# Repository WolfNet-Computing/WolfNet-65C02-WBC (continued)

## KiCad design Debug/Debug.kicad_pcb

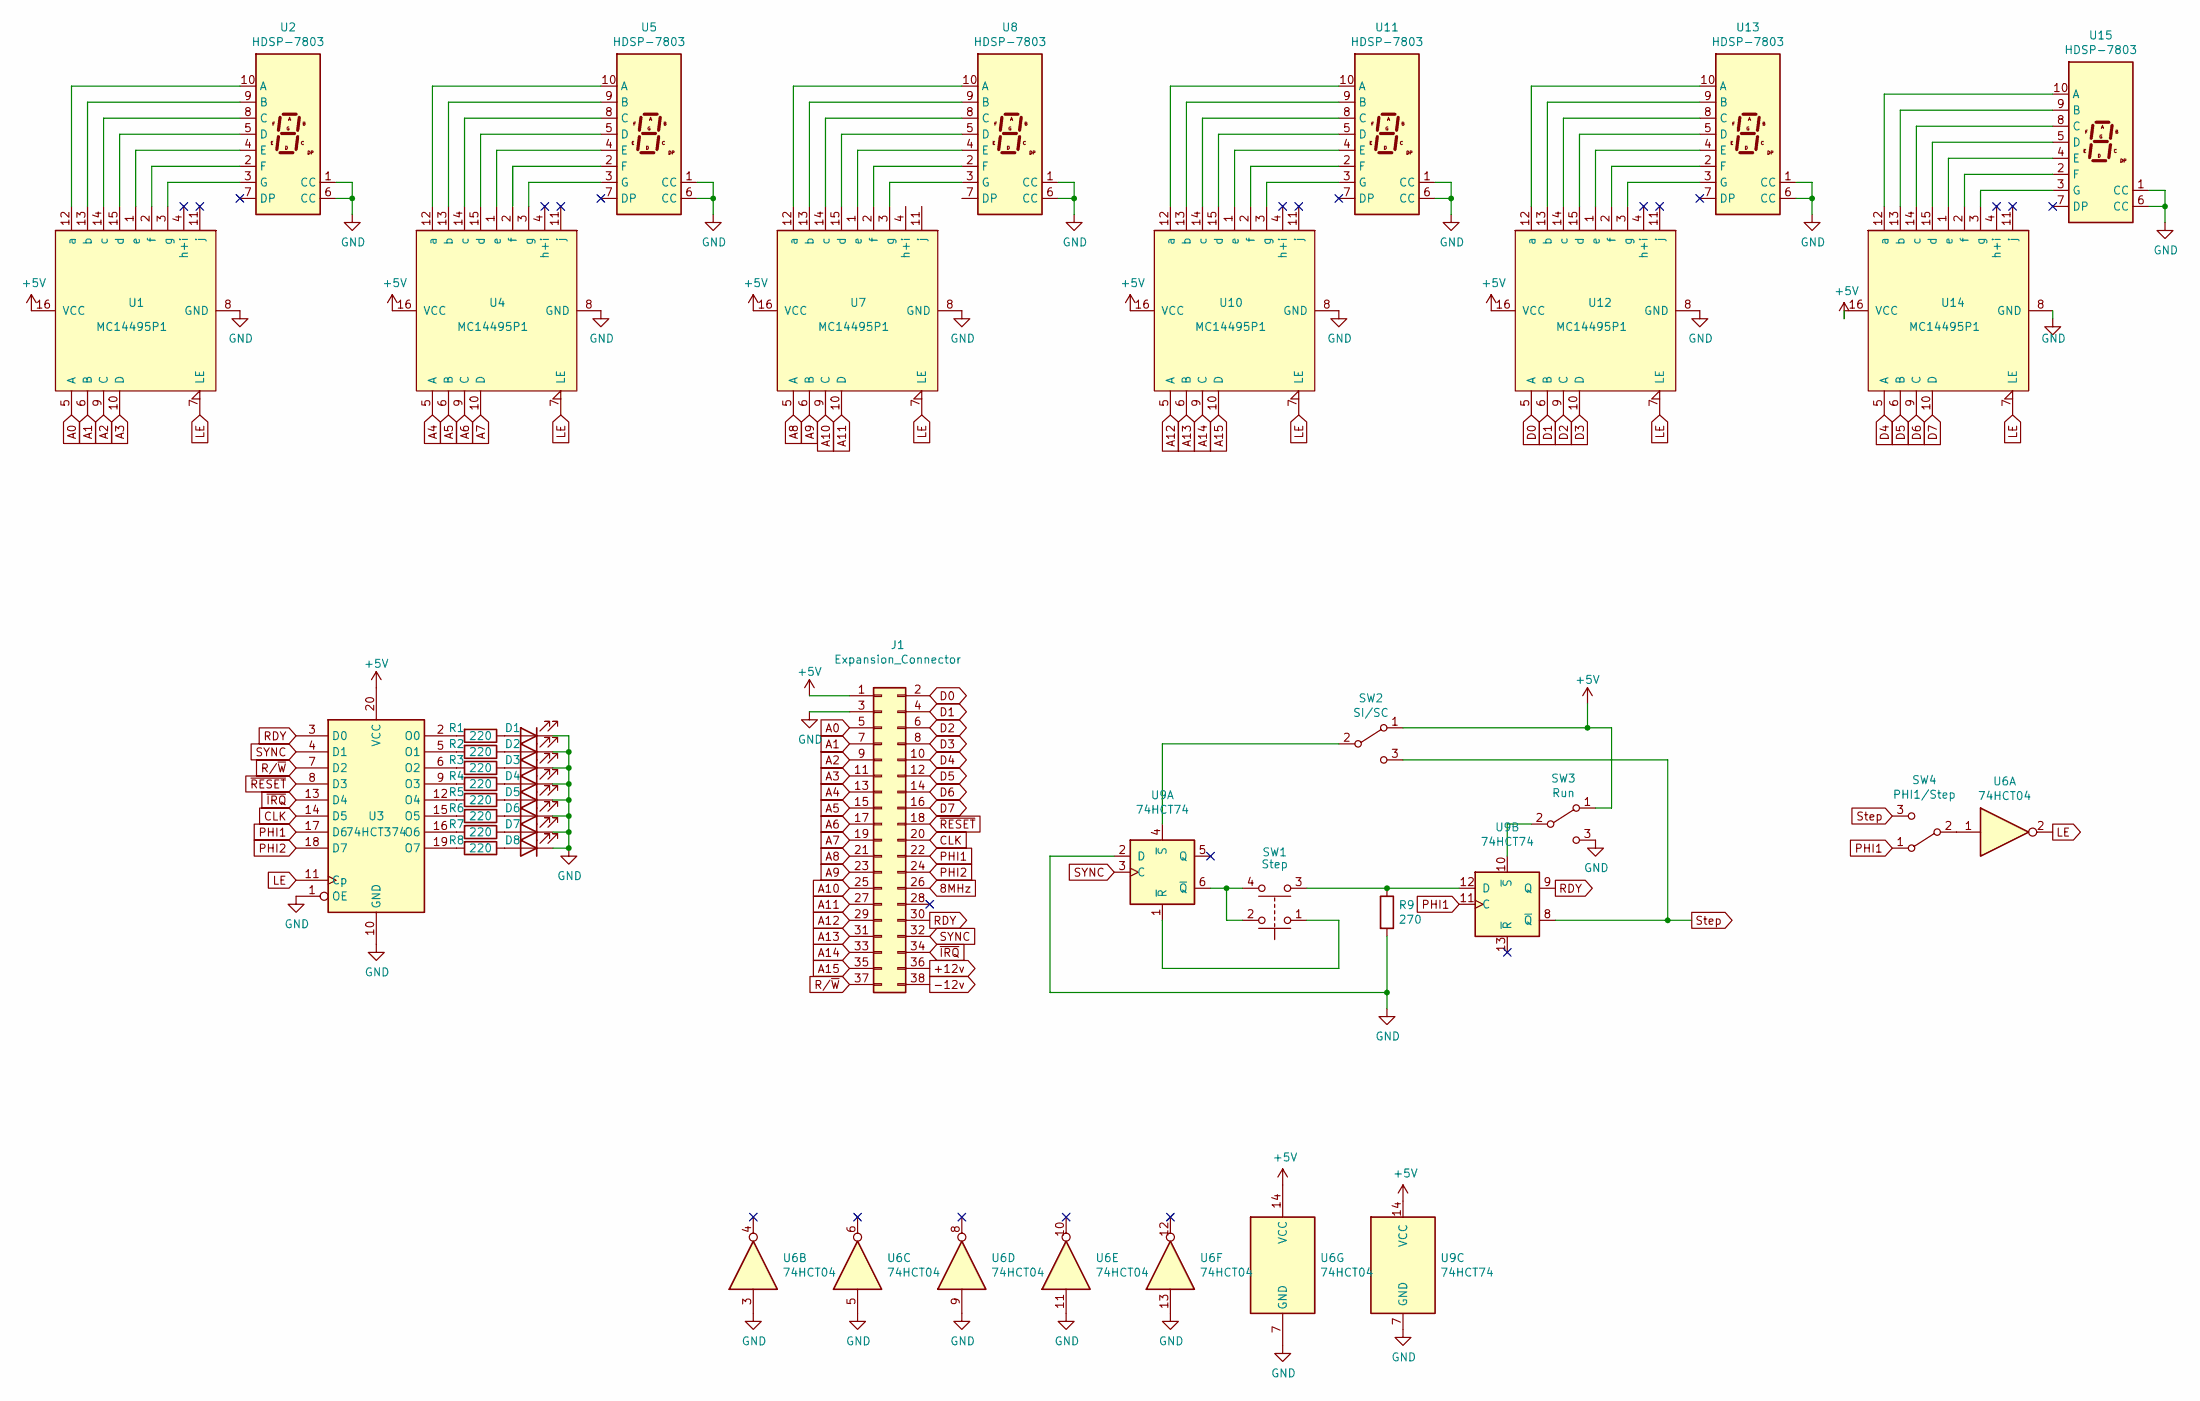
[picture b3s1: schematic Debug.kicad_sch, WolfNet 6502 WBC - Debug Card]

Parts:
D1: RDY; LED_D5.0mm
D2: Sync; LED_D5.0mm
D3: RW; LED_D5.0mm
D4: Reset; LED_D5.0mm
D5: IRQ; LED_D5.0mm
D6: NMI; LED_D5.0mm
D7: PHI1; LED_D5.0mm
D8: PHI2; LED_D5.0mm
J1: Expansion_Connector; PinHeader_2x19_P2.54mm_Horizontal
R1, R2, R3, R4, R5, R6, R7, R8: 220; R_Axial_DIN0207_L6.3mm_D2.5mm_P7.62mm_Horizontal
R9: 270; R_Axial_DIN0207_L6.3mm_D2.5mm_P7.62mm_Horizontal
SW1: Step; SW_Push_2P1T_Toggle_CK_PVA1xxH1xxxxxxV2
SW2: SI/SC; SW_Slide_1P2T_CK_OS102011MS2Q
SW3: Run; SW_Slide_1P2T_CK_OS102011MS2Q
SW4: PHI1/Step; SW_Slide_1P2T_CK_OS102011MS2Q
U1, U4, U7, U10, U12, U14: MC14495P1; DIP-16_W7.62mm_Socket_LongPads
U2, U5, U8, U11, U13, U15: HDSP-7803; HDSP-7801
U3: 74HCT374; DIP-20_W7.62mm_Socket_LongPads
U6: 74HCT04; DIP-14_W7.62mm_Socket_LongPads
U9: 74HCT74; DIP-14_W7.62mm_Socket_LongPads

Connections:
8MHz: J1.26
+5V: J1.1, SW2.1 (A), SW3.1 (A), U1.16 (VCC), U3.20 (VCC), U4.16 (VCC), U6.14 (VCC), U7.16 (VCC), U9.14 (VCC), U10.16 (VCC), U12.16 (VCC), U14.16 (VCC)
+12v: J1.36
-12v: J1.38
A0: J1.5, U1.5 (A)
A1: J1.7, U1.6 (B)
A2: J1.9, U1.9 (C)
A3: J1.11, U1.10 (D)
A4: J1.13, U4.5 (A)
A5: J1.15, U4.6 (B)
A6: J1.17, U4.9 (C)
A7: J1.19, U4.10 (D)
A8: J1.21, U7.5 (A)
A9: J1.23, U7.6 (B)
A10: J1.25, U7.9 (C)
A11: J1.27, U7.10 (D)
A12: J1.29, U10.5 (A)
A13: J1.31, U10.6 (B)
A14: J1.33, U10.9 (C)
A15: J1.35, U10.10 (D)
CLK: J1.20, U3.14 (D5)
D0: J1.2, U12.5 (A)
D1: J1.4, U12.6 (B)
D2: J1.6, U12.9 (C)
D3: J1.8, U12.10 (D)
D4: J1.10, U14.5 (A)
D5: J1.12, U14.6 (B)
D6: J1.14, U14.9 (C)
D7: J1.16, U14.10 (D)
GND: D1.1 (K), D2.1 (K), D3.1 (K), D4.1 (K), D5.1 (K), D6.1 (K), D7.1 (K), D8.1 (K), J1.3, R9.2, SW3.3 (C), U1.8 (GND), U2.1 (CC), U2.6 (CC), U3.1 (OE), U3.10 (GND), U4.8 (GND), U5.1 (CC), U5.6 (CC), U6.3, U6.5, U6.7 (GND), U6.9, U6.11, U6.13, U7.8 (GND), U8.1 (CC), U8.6 (CC), U9.2 (D), U9.7 (GND), U10.8 (GND), U11.1 (CC), U11.6 (CC), U12.8 (GND), U13.1 (CC), U13.6 (CC), U14.8 (GND), U15.1 (CC), U15.6 (CC)
LE: U1.7 (LE), U3.11 (Cp), U4.7 (LE), U6.2, U7.7 (LE), U10.7 (LE), U12.7 (LE), U14.7 (LE)
unnamed: D1.2 (A), R1.1
unnamed: D2.2 (A), R2.1
unnamed: D3.2 (A), R3.1
unnamed: D4.2 (A), R4.1
unnamed: D5.2 (A), R5.1
unnamed: D6.2 (A), R6.1
unnamed: D7.2 (A), R7.1
unnamed: D8.2 (A), R8.1
unnamed: SW2.2 (B), U9.4 (~S)
unnamed: SW3.2 (B), U9.10 (~S)
unnamed: SW4.2 (B), U6.1
unnamed: U1.12 (a), U2.10 (A)
unnamed: U1.13 (b), U2.9 (B)
unnamed: U1.14 (c), U2.8 (C)
unnamed: U1.15 (d), U2.5 (D)
unnamed: U1.1 (e), U2.4 (E)
unnamed: U1.2 (f), U2.2 (F)
unnamed: U1.3 (g), U2.3 (G)
unnamed: R1.2, U3.2 (O0)
unnamed: R2.2, U3.5 (O1)
unnamed: R3.2, U3.6 (O2)
unnamed: R4.2, U3.9 (O3)
unnamed: R5.2, U3.12 (O4)
unnamed: R6.2, U3.15 (O5)
unnamed: R7.2, U3.16 (O6)
unnamed: R8.2, U3.19 (O7)
unnamed: U4.12 (a), U5.10 (A)
unnamed: U4.13 (b), U5.9 (B)
unnamed: U4.14 (c), U5.8 (C)
unnamed: U4.15 (d), U5.5 (D)
unnamed: U4.1 (e), U5.4 (E)
unnamed: U4.2 (f), U5.2 (F)
unnamed: U4.3 (g), U5.3 (G)
unnamed: U7.12 (a), U8.10 (A)
unnamed: U7.13 (b), U8.9 (B)
unnamed: U7.14 (c), U8.8 (C)
unnamed: U7.15 (d), U8.5 (D)
unnamed: U7.1 (e), U8.4 (E)
unnamed: U7.2 (f), U8.2 (F)
unnamed: U7.3 (g), U8.3 (G)
unnamed: SW1.2, SW1.4, U9.6 (~Q)
unnamed: SW1.1, U9.1 (~R)
unnamed: R9.1, SW1.3, U9.12 (D)
unnamed: U10.12 (a), U11.10 (A)
unnamed: U10.13 (b), U11.9 (B)
unnamed: U10.14 (c), U11.8 (C)
unnamed: U10.15 (d), U11.5 (D)
unnamed: U10.1 (e), U11.4 (E)
unnamed: U10.2 (f), U11.2 (F)
unnamed: U10.3 (g), U11.3 (G)
unnamed: U12.12 (a), U13.10 (A)
unnamed: U12.13 (b), U13.9 (B)
unnamed: U12.14 (c), U13.8 (C)
unnamed: U12.15 (d), U13.5 (D)
unnamed: U12.1 (e), U13.4 (E)
unnamed: U12.2 (f), U13.2 (F)
unnamed: U12.3 (g), U13.3 (G)
unnamed: U14.12 (a), U15.10 (A)
unnamed: U14.13 (b), U15.9 (B)
unnamed: U14.14 (c), U15.8 (C)
unnamed: U14.15 (d), U15.5 (D)
unnamed: U14.1 (e), U15.4 (E)
unnamed: U14.2 (f), U15.2 (F)
unnamed: U14.3 (g), U15.3 (G)
PHI1: J1.22, SW4.1 (A), U3.17 (D6), U9.11 (C)
PHI2: J1.24, U3.18 (D7)
RDY: J1.30, U3.3 (D0), U9.9 (Q)
R/~W: J1.37, U3.7 (D2)
SYNC: J1.32, U3.4 (D1), U9.3 (C)
Step: SW2.3 (C), SW4.3 (C), U9.8 (~Q)
~IRQ: J1.34, U3.13 (D4)
~RESET: J1.18, U3.8 (D3)

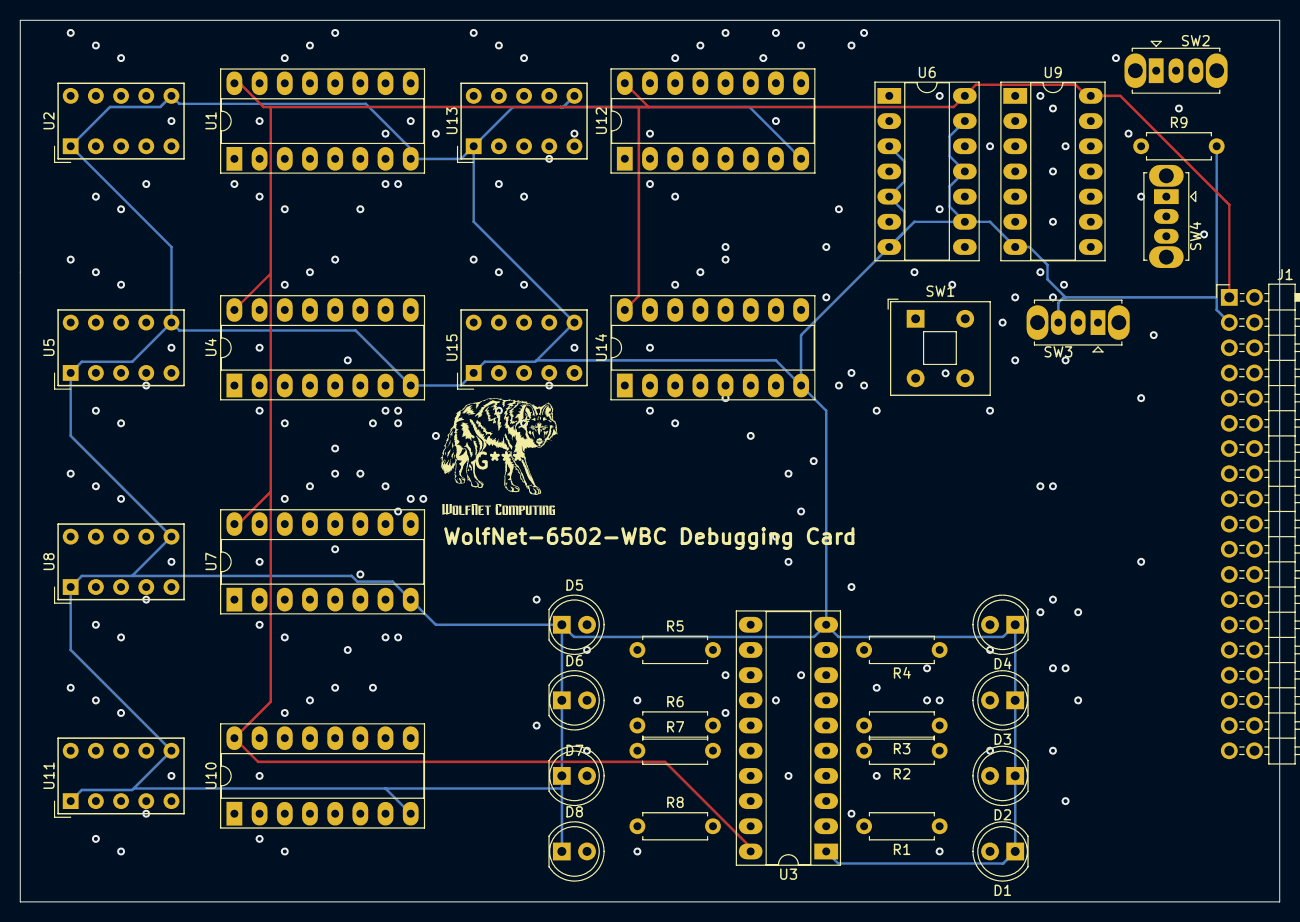
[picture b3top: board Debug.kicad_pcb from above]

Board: 4 copper layers, 127.0 x 88.9 mm, 37 parts (0 on the bottom side), 100 nets.

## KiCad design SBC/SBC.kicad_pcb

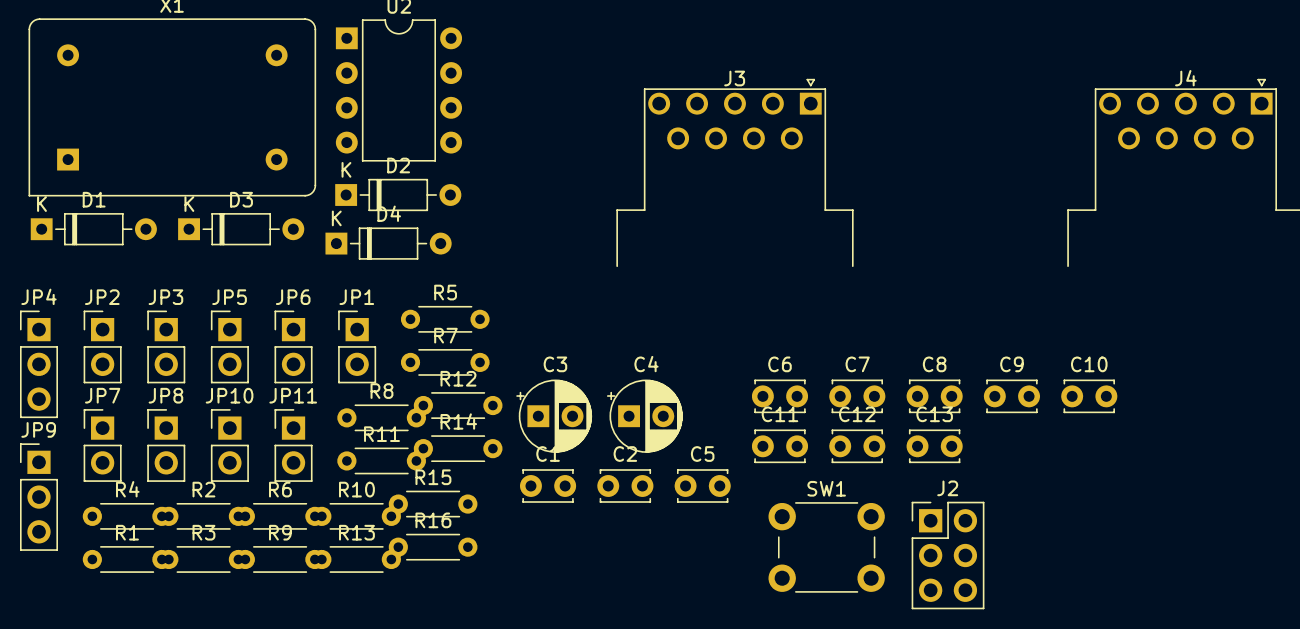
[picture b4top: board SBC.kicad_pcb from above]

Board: 2 copper layers, 50 parts (0 on the bottom side), 14 nets, no tracks yet.

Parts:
C1, C2, C5, C6, C7, C8, C9, C10, C11, C12, C13: C; C_Disc_D3.4mm_W2.1mm_P2.50mm
C3, C4: CP; CP_Radial_D5.0mm_P2.50mm
D1, D2, D3, D4: 1N4148; D_DO-35_SOD27_P7.62mm_Horizontal
J2: GPIO_Connector; PinHeader_2x03_P2.54mm_Vertical
J3, J4: DB9_Male; DSUB-9_Female_Horizontal_P2.77x2.54mm_EdgePinOffset9.40mm
JP1, JP2, JP3, JP6, JP7, JP8, JP10: Jumper_2_Bridged; PinHeader_1x02_P2.54mm_Vertical
JP4: Jumper_3_Open; PinHeader_1x03_P2.54mm_Vertical
JP5, JP11: Jumper_2_Open; PinHeader_1x02_P2.54mm_Vertical
JP9: Jumper_3_Bridged12; PinHeader_1x03_P2.54mm_Vertical
R1, R2, R3: 3.3k; R_Axial_DIN0204_L3.6mm_D1.6mm_P5.08mm_Horizontal
R4, R5, R6, R7, R8, R9, R10, R11, R12, R13, R14, R15, R16: R; R_Axial_DIN0204_L3.6mm_D1.6mm_P5.08mm_Horizontal
SW1: SW_Push; SW_PUSH_6mm
U2: NE555P; DIP-8_W7.62mm
X1: ACO-xxxMHz; Oscillator_DIP-14

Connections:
CLK: JP6.2, JP7.2, JP8.2
CLK1: JP6.1, X1.8
GND: C1.2, C2.2, C3.2, C4.2, C5.2, C6.2, C7.2, C8.2, C9.2, C10.1, C11.1, C12.1, C13.1, D1.2, D3.1, J3.5, J3.9, J4.5, J4.9, JP3.1, R16.1, SW1.2, U2.1, X1.7
unnamed: C1.1, SW1.1, U2.2
unnamed: C3.1, R4.2, U2.6, U2.7
unnamed: C4.1, D2.1, D4.2, JP4.3
unnamed: C7.1, JP4.2, JP5.1
unnamed: D1.1, D2.2
unnamed: D3.2, D4.1
unnamed: JP1.2, R3.1
unnamed: JP2.2, R2.1
unnamed: JP10.2, R16.2
PG: JP10.1, JP11.1
VCC: C2.1, C5.1, C6.1, C8.1, C9.1, C10.2, C11.2, C12.2, C13.2, JP5.2, R1.2, R2.2, R3.2, R4.1, R5.2, R6.1, R7.1, R8.1, R9.1, R10.1, R11.1, R12.1, R13.1, R14.1, R15.2, U2.4, U2.8, X1.14

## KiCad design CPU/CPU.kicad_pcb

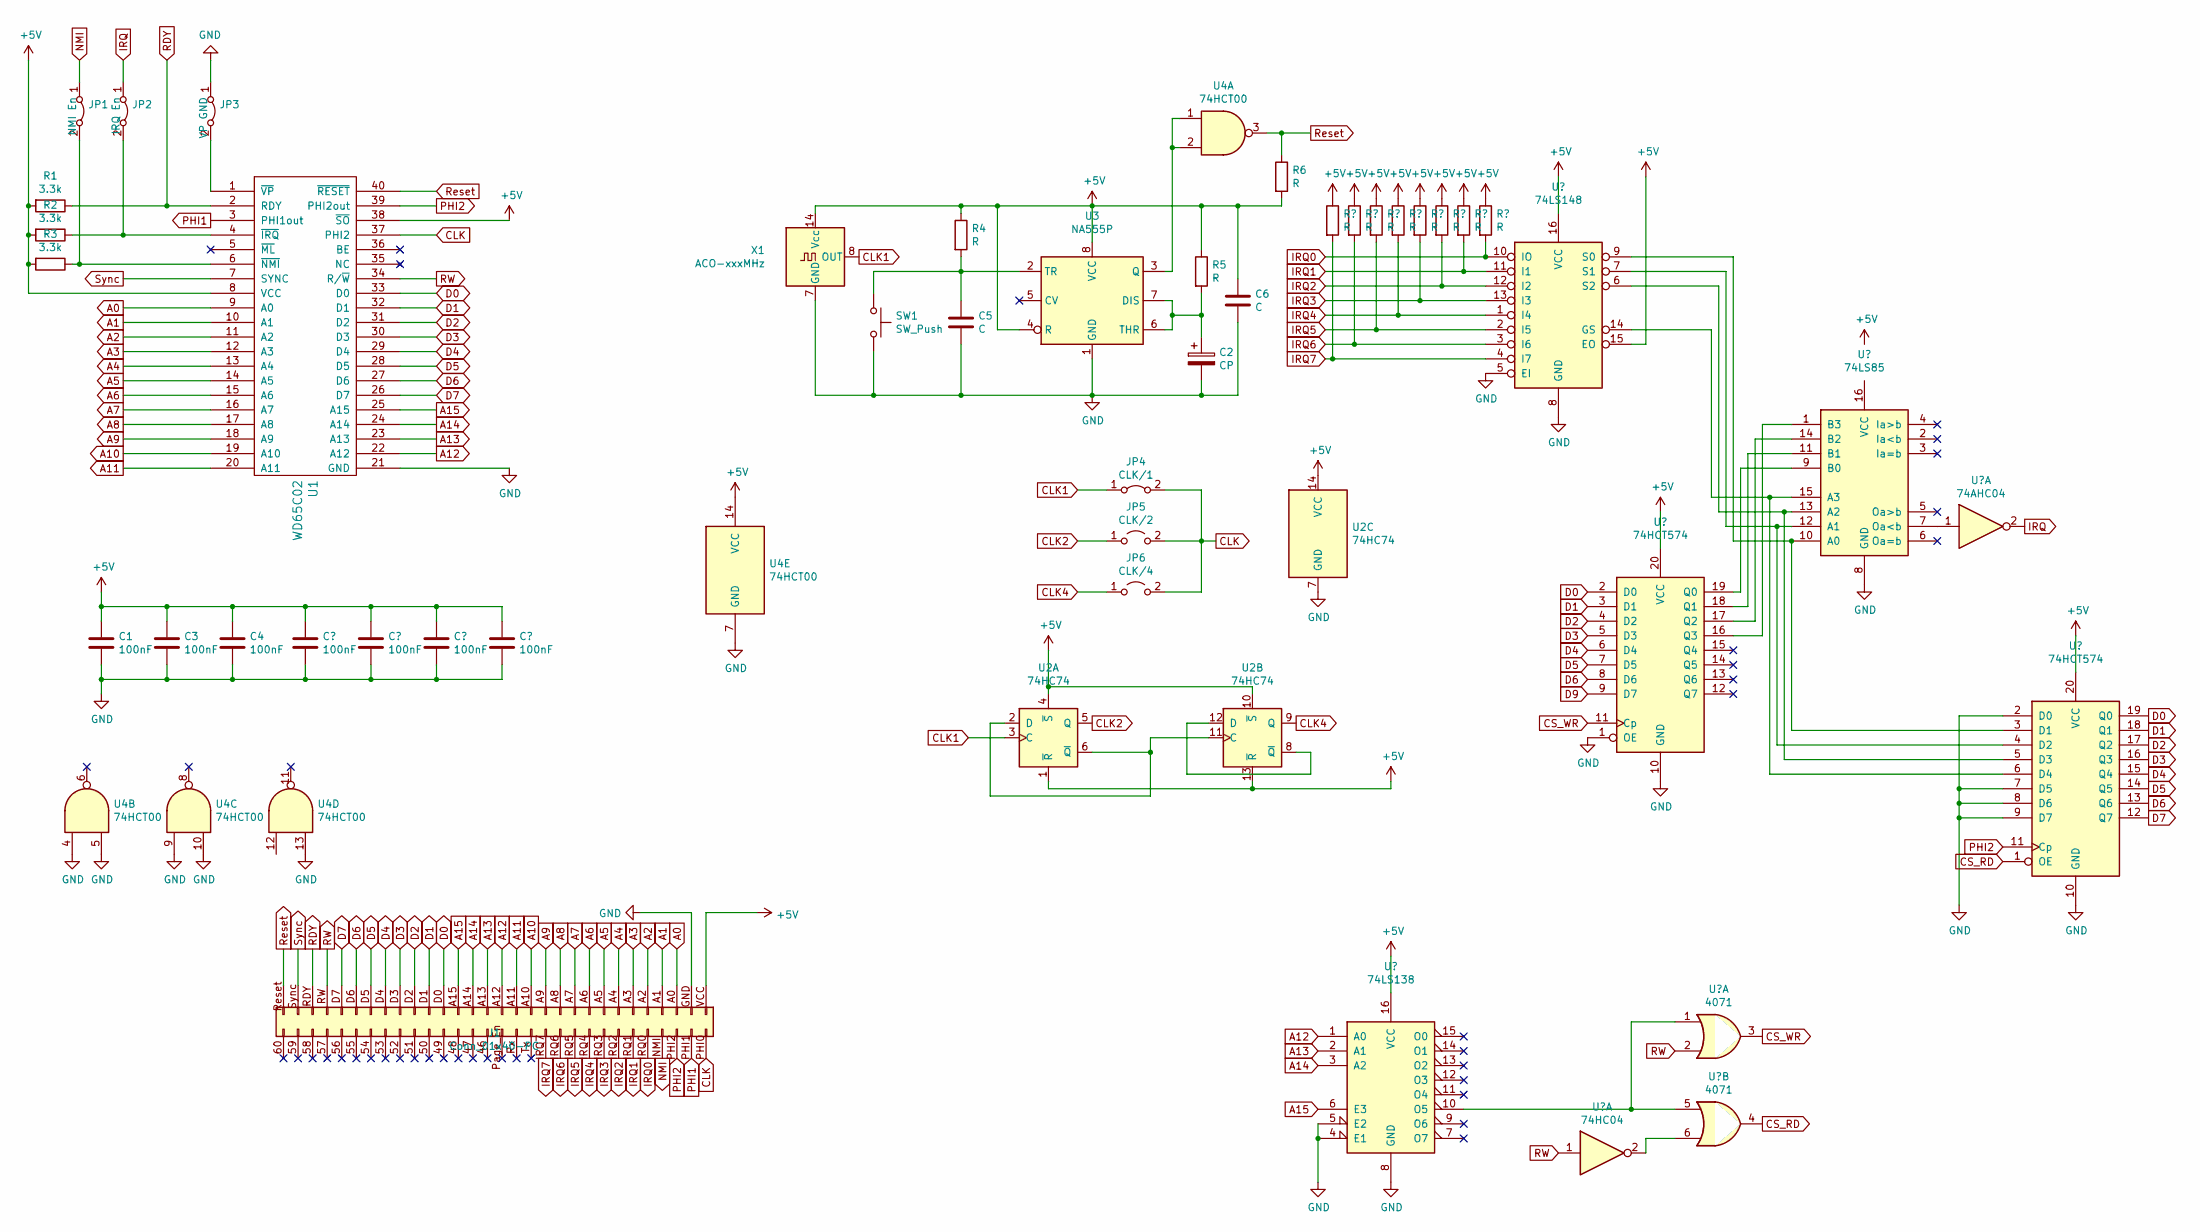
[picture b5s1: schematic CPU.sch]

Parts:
C1, C3, C4: 100nF; C_Disc_D5.0mm_W2.5mm_P5.00mm
C2: CP; CP_Radial_D6.3mm_P2.50mm
C5, C6: C; C_Disc_D5.0mm_W2.5mm_P5.00mm
J1: Conn_01x40-PC; BaseboardConnector_Male
JP1: NMI En; PinHeader_1x02_P2.54mm_Vertical
JP2: IRQ En; PinHeader_1x02_P2.54mm_Vertical
JP3: VP GND; PinHeader_1x02_P2.54mm_Vertical
JP4: CLK/1; PinHeader_1x02_P2.54mm_Vertical
JP5: CLK/2; PinHeader_1x02_P2.54mm_Vertical
JP6: CLK/4; PinHeader_1x02_P2.54mm_Vertical
R1, R2, R3: 3.3k; R_Axial_DIN0207_L6.3mm_D2.5mm_P7.62mm_Horizontal
R4, R5, R6: R; R_Axial_DIN0207_L6.3mm_D2.5mm_P7.62mm_Horizontal
SW1: SW_Push; SW_PUSH_6mm
U1: WD65C02; DIP-40_W25.4mm_Socket_LongPads
U2: 74HC74; DIP-16_W7.62mm_Socket_LongPads
U3: NA555P; DIP-8_W7.62mm
U4: 74HCT00
X1: ACO-xxxMHz; Oscillator_DIP-14

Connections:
+5V: C1.1, C3.1, C4.1, C6.1, J1.VCC, R1.2, R2.2, R3.2, R4.1, R5.1, R6.2, U1.8 (VCC), U1.38 (~SO), U2.1 (~R), U2.4 (~S), U2.10 (~S), U2.13 (~R), U2.14 (VCC), U3.4 (R), U3.8 (VCC), U4.14 (VCC), X1.14 (Vcc)
A0: J1.A0, U1.9 (A0)
A1: J1.A1, U1.10 (A1)
A2: J1.A2, U1.11 (A2)
A3: J1.A3, U1.12 (A3)
A4: J1.A4, U1.13 (A4)
A5: J1.A5, U1.14 (A5)
A6: J1.A6, U1.15 (A6)
A7: J1.A7, U1.16 (A7)
A8: J1.A8, U1.17 (A8)
A9: J1.A9, U1.18 (A9)
A10: J1.A10, U1.19 (A10)
A11: J1.A11, U1.20 (A11)
A12: J1.A12, U1.22 (A12)
A13: J1.A13, U1.23 (A13)
A14: J1.A14, U1.24 (A14)
A15: J1.A15, U1.25 (A15)
CLK: J1.PHI0, JP4.2 (B), JP5.2 (B), JP6.2 (B), U1.37 (PHI2)
CLK1: JP4.1 (A), U2.3 (C), X1.8 (OUT)
CLK2: JP5.1 (A), U2.5 (Q)
CLK4: JP6.1 (A), U2.9 (Q)
D0: J1.D0, U1.33 (D0)
D1: J1.D1, U1.32 (D1)
D2: J1.D2, U1.31 (D2)
D3: J1.D3, U1.30 (D3)
D4: J1.D4, U1.29 (D4)
D5: J1.D5, U1.28 (D5)
D6: J1.D6, U1.27 (D6)
D7: J1.D7, U1.26 (D7)
GND: C1.2, C2.2, C3.2, C4.2, C5.2, C6.2, J1.GND, JP3.1 (A), SW1.2, U1.21 (GND), U2.7 (GND), U3.1 (GND), U4.4, U4.5, U4.7 (GND), U4.9, U4.10, U4.12, U4.13, X1.7 (GND)
IRQ: JP2.1 (A)
NMI: J1.NMI, JP1.1 (A)
unnamed: C2.1, R5.2, U3.6 (THR), U3.7 (DIS)
unnamed: C5.1, R4.2, SW1.1, U3.2 (TR)
unnamed: JP1.2 (B), R3.1, U1.6 (~NMI)
unnamed: JP2.2 (B), R2.1, U1.4 (~IRQ)
unnamed: JP3.2 (B), U1.1 (~VP)
unnamed: J1.PHI1, U1.3 (PHI1out)
unnamed: U2.2 (D), U2.6 (~Q), U2.11 (C)
unnamed: U2.8 (~Q), U2.12 (D)
unnamed: U3.3 (Q), U4.1, U4.2
PHI2: J1.PHI2, U1.39 (PHI2out)
RDY: J1.RDY, R1.1, U1.2 (RDY)
RW: J1.RW, U1.34 (R/~W)
Reset: J1.Reset, R6.1, U1.40 (~RESET), U4.3
Sync: J1.Sync, U1.7 (SYNC)

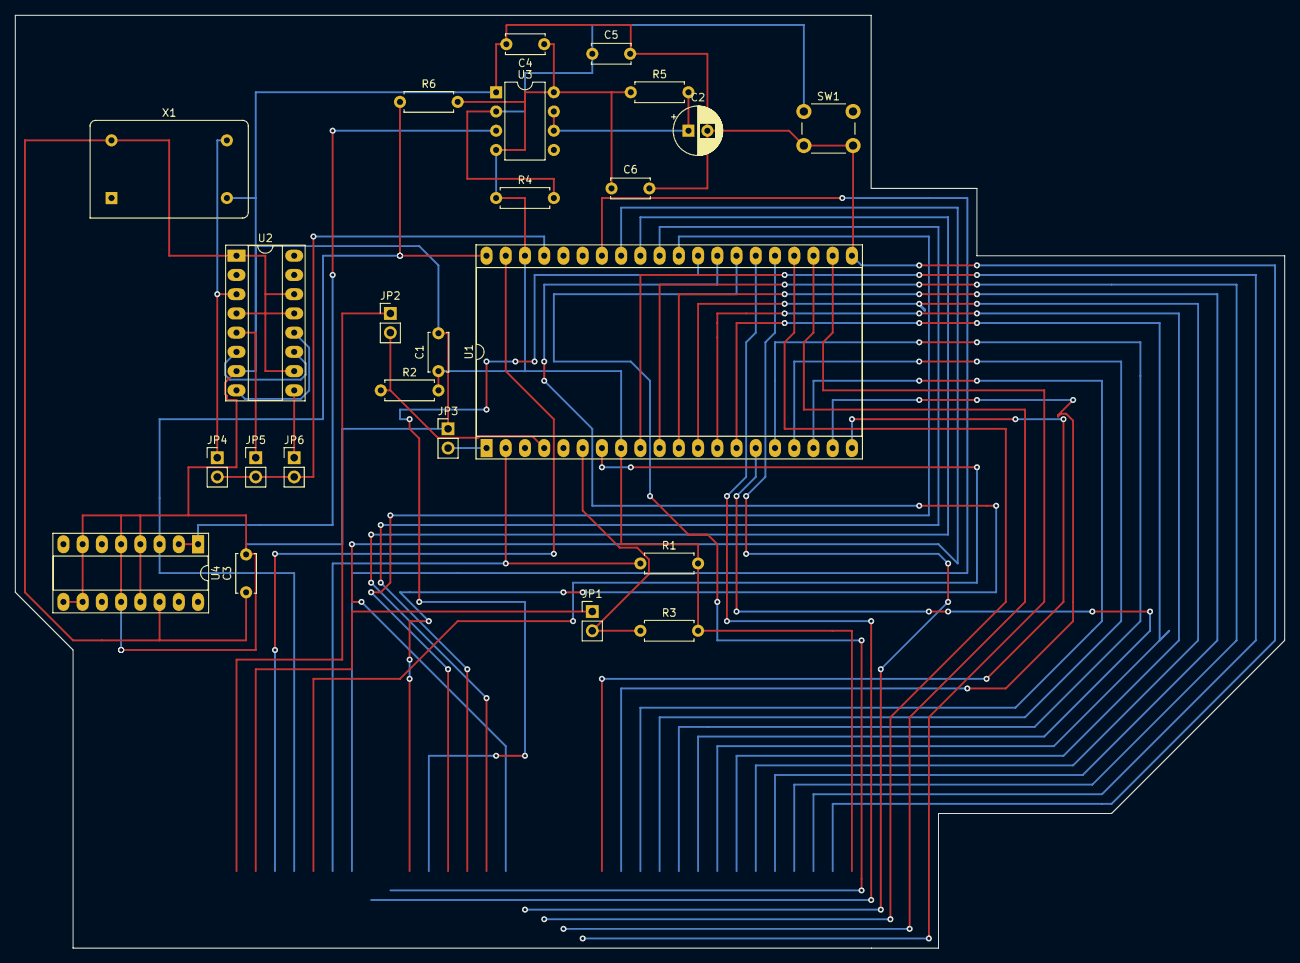
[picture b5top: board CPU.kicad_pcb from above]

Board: 2 copper layers, 167.6 x 123.2 mm, 24 parts (0 on the bottom side), 16 nets.

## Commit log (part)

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2022-04-23 Finalised 2.1 of the schematic and circuit board...
2022-04-23 Set theme jekyll-theme-minimal
2022-04-23 Create CNAME
2022-04-23 Set theme jekyll-theme-slate
2022-04-23 Create LICENSE
2022-04-23 Debugging card added...
2022-04-24 Fixed grounding issue...
2022-04-25 Updated the things...
2022-04-25 Gerber files generated...
2022-04-26 2.3 ON THE WAY...
2022-04-26 On our way to 2.3...
2022-04-26 documentation improvements...
2022-04-26 Licensing organised...
2022-04-26 Reformatted visually but not legally...
2022-04-27 Sound generator and memory banking added...
2022-04-27 Updated component references...
2022-04-27 Pre-annotation upload...
2022-04-27 Improvements and bug fixes...
2022-04-27 Started PCB design...
2022-04-28 Separated sounds card from motherboard...
    This is only to save space on the final motherboard design.
2022-04-28 Part way to bank switched memory...
2022-04-28 Documentation re-added...
2022-04-28 Completed schematic for 2.3...
2022-04-28 Bug fixes...
    Multiple components had the same name, this has been corrected.
2022-04-30 Bug fixes and added some traces...
2022-05-01 More traces added...
2022-05-01 Added more traces...
2022-05-01 630 odd traces left to go...
2022-05-01 549 traces to go...
2022-05-01 525 traces to go...
2022-05-01 Well on the road to 2.3...
2022-05-01 Update pinouts.md
    TODO: FINISH HIM!
2022-05-01 500 odd traces left...
2022-05-01 Documentation location changed...
2022-05-02 Caps, Power for gates and traces added...
2022-05-02 539 traces to go...
2022-05-02 522 traces to go...
2022-05-02 488 traces to go...
2022-05-02 480 traces left to go...
2022-05-02 A lot closer now...
2022-05-02 Created motherboard.md
2022-05-02 Removed some old 2.2 files...
2022-05-02 420 traces to go...
    420! 420!! 420!!!
2022-05-02 202 traces until 2.3...
2022-05-02 168 traces to go...
2022-05-02 156 unrouted traces...
2022-05-03 81 more traces...
2022-05-03 Finished routing traces...
2022-05-03 Final traces added and fills added...
2022-05-03 2.3 has arrived...
    2.3! 2.3!! 2.3!!!
2022-05-03 Bug fixes...
2022-05-04 Bug fixes and shutdown button added...
2022-05-04 Updated documentation location...
2022-05-04 Beautified documentation...
2022-05-04 Edited docs...
2022-05-04 Renamed some components...
2022-05-04 Sound card schematic completed...
2022-05-04 Completed Sound Card...
2022-05-04 Debug card added...
2022-05-04 Started video card...
2022-05-05 Updated motherboard PCB and finished sound card PCB...
    Website added to PCB design and completed sound card schematic, PCB and SVG files.
2022-05-05 Added modified ISA bus to PC libraries...
2022-05-06 Updated motherboard...
2022-05-06 Added wolf symbol...
2022-05-06 65C51N changed to 65C51...
2022-05-08 Added video card project files...
2022-05-08 Updated libraries and started video card...
2022-05-08 Updated video card...
2022-05-08 v2.5...
    2.5 is here!
2022-05-09 Road to 2.5...
    Still need to update address decoding to use 74HCT138s
2022-05-09 2.5 schematic complete...
2022-05-09 Road to 2.5 release...
2022-05-09 Started on 2.5 PCB...
2022-05-10 Almost finished 2.5 placements...
2022-05-10 Finished 2.5 placement...
2022-05-11 550 unrouted traces...
2022-05-11 527 unrouted traces...
    Updated documentation in HTML.
2022-05-11 500 unrouted traces...
2022-05-11 485 unrouted traces...
2022-05-11 Fat trimming...
    Trimmed out some old files and edited the docs.
2022-05-11 455 unrouted traces...
2022-05-11 412 traces left to route...
2022-05-11 406 traces left to route...
2022-05-11 405 unrouted traces...
2022-05-11 357 traces left to route...
2022-05-11 Documentation updated...
2022-05-12 316 traces left to route...
2022-05-12 Updated pinout documentation...
2022-05-12 311 traces to route...
2022-05-12 290 unrouted traces...
2022-05-12 Backups...
2022-05-12 286 unrouted traces...
2022-05-12 257 unrouted traces...
2022-05-12 247 unrouted traces...
2022-05-12 243 unrouted traces...
2022-05-12 239 unrouted traces...
2022-05-12 233 unrouted traces...
2022-05-13 214 unrouted traces...
2022-05-13 173 unrouted traces...
2022-05-13 157 unrouted traces...
2022-05-13 149 unrouted traces...
2022-05-14 Finished sound card...
2022-05-14 136 unrouted traces...
2022-05-14 111 unrouted traces...
2022-05-14 96 traces left to route...
2022-05-14 92 unrouted traces...
2022-05-15 Reduced chip count...
2022-05-15 646 unrouted traces...
2022-05-15 438 unrouted traces...
2022-05-15 372 unrouted traces...
2022-05-15 Internal file management...
2022-05-15 Optimised layout...
2022-05-15 Updated layout and form factor...
2022-05-15 298 unrouted traces...
2022-05-15 246 unrouted traces...
2022-05-15 226 unrouted traces...
2022-05-15 192 unrouted traces...
2022-05-15 Updated iBOM and version...
2022-05-16 203 unrouted traces...
2022-05-16 Updated documentation...
2022-05-16 153 unrouted traces...
2022-05-16 150 unrouted traces...
2022-05-16 114 unrouted traces...
2022-05-16 110 unrouted traces...
2022-05-16 104 unrouted traces...
2022-05-16 100 unrouted traces...
2022-05-16 78 unrouted traces...
2022-05-16 Updated logo...
2022-05-16 69 unrouted traces...
2022-05-16 43 unrouted traces...
2022-05-16 Updated worksheet...
2022-05-17 16 unrouted traces...
2022-05-17 Completed version 2.6...
2022-05-17 Finished sound card 1.2...
2022-05-17 Added prototyping card...
2022-05-17 Updated debug card...
2022-05-18 Debug card layout completed...
2022-05-18 Prototyping updated...
2022-05-18 6 unrouted traces...
2022-05-18 Version 2.6 completed...
2022-05-18 Prototyping card updated...
2022-05-18 98 unrouted traces...
2022-05-18 Logo added...
2022-05-18 Updated images...
2022-05-18 90 unrouted traces...
2022-05-20 Completed 2.7...
2022-05-20 Updated motherboard info...
2022-05-20 64 unrouted traces...
2022-05-21 59 unrouted traces...
2022-05-21 45 unrouted traces...
2022-05-21 36 unrouted traces...
2022-05-21 Completed debugging card...
2022-05-21 Finished routing traces on motherboard...
2022-05-24 Video card added...
2022-05-24 Added reference files...
2022-05-26 Added components...
2022-05-27 Updated motherboard and video card schematics...
2022-06-27 Updated to include BS 3939 compliance...
2022-08-15 Updated to fit some standard I can't recall...
2022-09-10 Updated file locations...
2022-09-20 Updated site...
2022-10-27 Create Motherboard.kicad_sch-bak
2022-11-01 Moved files to KiCAD-Libraries...
